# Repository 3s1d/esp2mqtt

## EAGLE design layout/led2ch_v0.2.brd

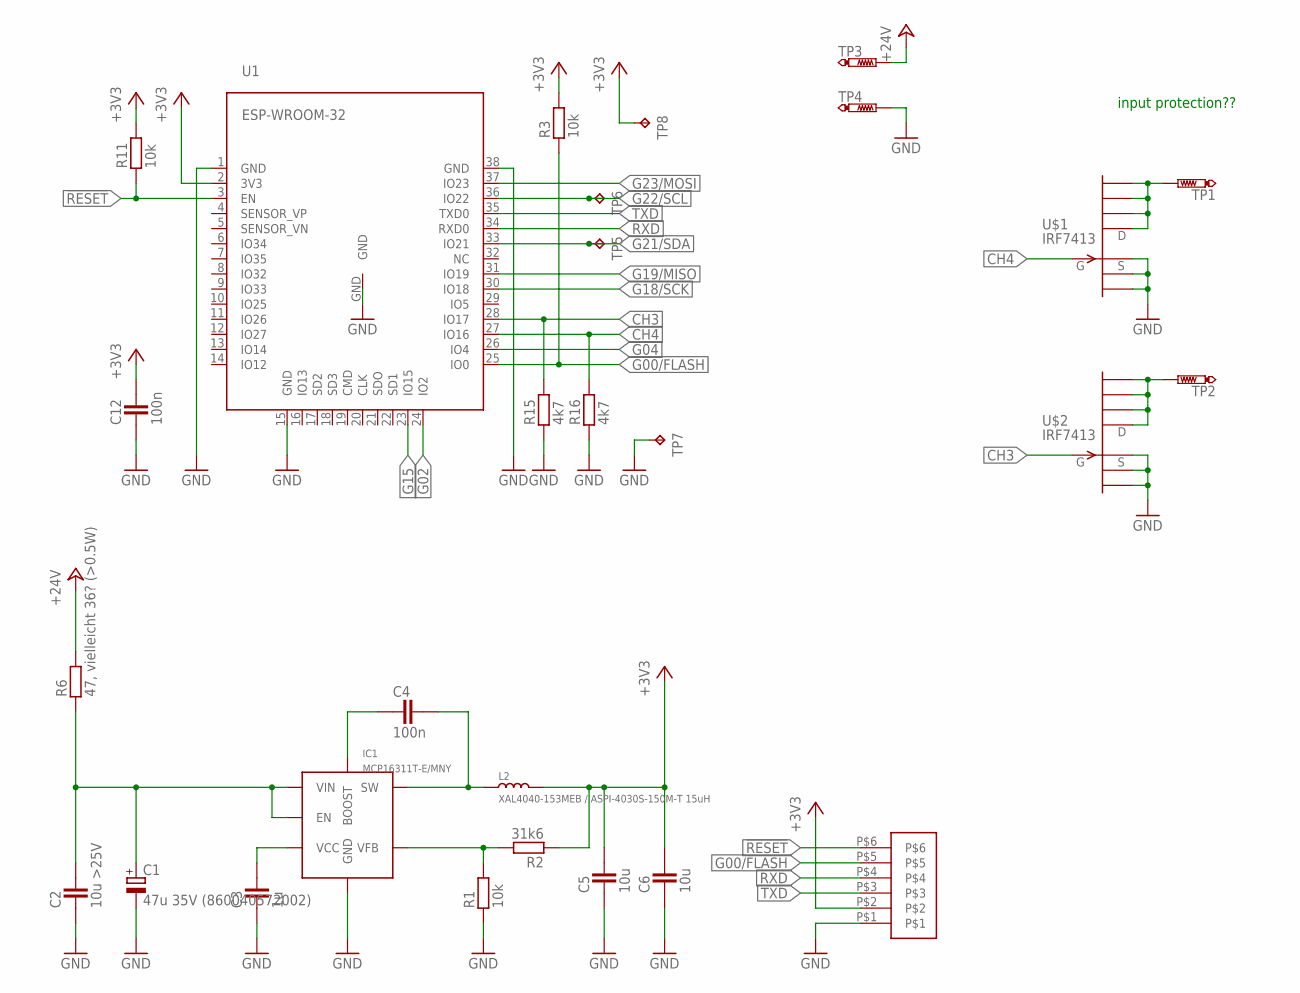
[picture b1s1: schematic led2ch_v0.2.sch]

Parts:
C1: 47u 35V (860040572002); E2-5
C2: 10u >25V; CAPC2012X145AN
C3: 1u; CAPC1608X92N
C4, C12: 100n; CAPC1005X60N
C5, C6: 10u; CAPC2012X145AN
IC1: MCP16311T-E/MNY; TDFN8
L2: XAL4040-153MEB / ASPI-4030S-150M-T 15uH; L0420
R1, R3, R11: 10k; RESC1005X40AN
R2: 31k6; RESC1005X40AN
R6: 47, vielleicht 36? (>0.5W); RESC3115X70N
R15, R16: 4k7; RESC1005X40AN
TP1, TP2: PTR1B1,27; B1,27
TP3, TP4: PTR1B2,54; B2,54
TP5, TP6, TP7, TP8: TPB1,27; B1,27
U1: ESP-WROOM-32
U$1, U$2: IRF7413; SO-8
U$3: 3X2-2.00RM

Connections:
!RESET: R11.1, U1.3 (EN), U$3.P$6
+3V3: C5.2, C6.2, C12.2, L2.2, R2.1, R3.2, R11.2, TP8.TP, U1.2 (3V3), U$3.P$2
+24V: R6.2, TP3.TP
CH3: R15.2, U1.28 (IO17), U$2.4 (G)
CH4: R16.2, U1.27 (IO16), U$1.4 (G)
G00/FLASH: R3.1, U1.25 (IO0), U$3.P$5
G02: U1.24 (IO2)
G04: U1.26 (IO4)
G15: U1.23 (IO15)
G18/SCK: U1.30 (IO18)
G19/MISO: U1.31 (IO19)
G21/SDA: TP5.TP, U1.33 (IO21)
G22/SCL: TP6.TP, U1.36 (IO22)
G23/MOSI: U1.37 (IO23)
GND: C1.-, C2.1, C3.1, C5.1, C6.1, C12.1, IC1.P$5 (GND), IC1.P$8 (GND), IC1.P$9 (GND), R1.1, R15.1, R16.1, TP4.TP, TP7.TP, U1.1 (GND), U1.15 (GND), U1.38 (GND), U1.GND, U$1.1 (S), U$1.2 (S1), U$1.3 (S2), U$2.1 (S), U$2.2 (S1), U$2.3 (S2), U$3.P$1
unnamed: C3.2, IC1.P$2 (VCC)
unnamed: C1.+, C2.2, IC1.P$3 (EN), IC1.P$4 (VIN), R6.1
unnamed: C4.1, IC1.P$7 (BOOST)
unnamed: C4.2, IC1.P$6 (SW), L2.1
unnamed: IC1.P$1 (VFB), R1.2, R2.2
unnamed: TP1.TP, U$1.5 (D), U$1.6 (D1), U$1.7 (D2), U$1.8 (D3)
unnamed: TP2.TP, U$2.5 (D), U$2.6 (D1), U$2.7 (D2), U$2.8 (D3)
RXD: U1.34 (RXD0), U$3.P$4
TXD: U1.35 (TXD0), U$3.P$3

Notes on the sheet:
input protection??

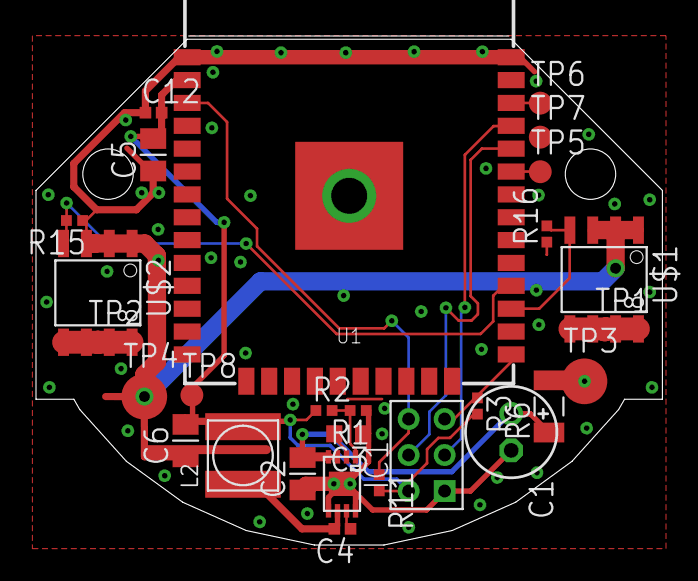
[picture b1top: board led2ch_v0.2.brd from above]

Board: 2 copper layers, 34.8 x 28.3 mm, 28 parts (0 on the bottom side), 18 nets.

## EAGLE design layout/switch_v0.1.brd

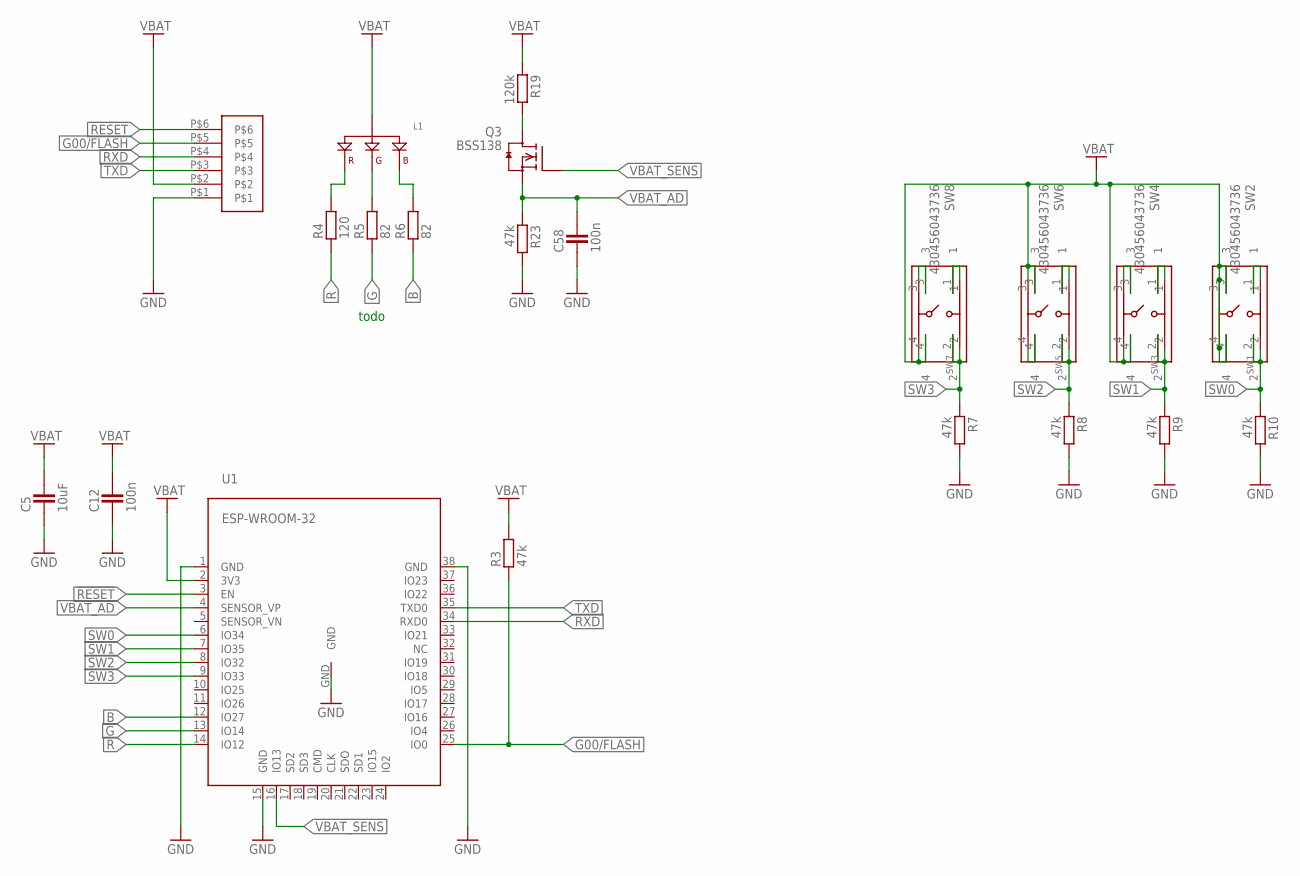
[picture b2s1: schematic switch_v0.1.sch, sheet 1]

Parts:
C5: 10uF; CAPC2012X145AN
C12, C58: 100n; CAPC1005X60N
L1: RGBLED_COMMONA; LEDRGB
Q3: BSS138; SOT23
R3, R7, R8, R9, R10, R23: 47k; RESC1005X40AN
R4: 120; RESC2012X70N
R5, R6: 82; RESC2012X70N
R19: 120k; RESC1005X40AN
SW1, SW3, SW5, SW7: 4301X20858X6
SW2, SW4, SW6, SW8: 430456043736
U1: ESP-WROOM-32
U$3: 3X2-2.00RM

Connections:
!RESET: U1.3 (EN), U$3.P$6; also elsewhere on the board
B: R6.1, U1.12 (IO27)
G: R5.1, U1.13 (IO14)
G00/FLASH: R3.1, U1.25 (IO0), U$3.P$5
GND: C5.1, C12.1, C58.1, R7.2, R8.2, R9.2, R10.2, R23.2, U1.1 (GND), U1.15 (GND), U1.38 (GND), U1.GND, U$3.P$1; also elsewhere on the board
unnamed: L1.1 (R), R4.2
unnamed: L1.3 (G), R5.2
unnamed: L1.4 (B), R6.2
unnamed: SW5.1, SW6.1
unnamed: SW5.4, SW6.4
unnamed: SW7.3, SW8.3
unnamed: SW7.1, SW8.1
unnamed: SW3.1, SW4.1
unnamed: SW3.3, SW4.3
unnamed: SW1.1, SW2.1
unnamed: Q3.3 (D), R19.2
R: R4.1, U1.14 (IO12)
RXD: U1.34 (RXD0), U$3.P$4
SW0: R10.1, SW1.2, SW2.2, U1.6 (IO34)
SW1: R9.1, SW3.2, SW4.2, U1.7 (IO35)
SW2: R8.1, SW5.2, SW6.2, U1.8 (IO32)
SW3: R7.1, SW7.2, SW8.2, U1.9 (IO33)
TXD: U1.35 (TXD0), U$3.P$3
VBAT: C5.2, C12.2, L1.2 (A), R3.2, R19.1, SW1.3, SW1.4, SW2.3, SW2.4, SW3.4, SW4.4, SW5.3, SW6.3, SW7.4, SW8.4, U1.2 (3V3), U$3.P$2; also elsewhere on the board
VBAT_AD: C58.2, Q3.2 (S), R23.1, U1.4 (SENSOR_VP)
VBAT_SENS: Q3.1 (G), U1.16 (IO13)

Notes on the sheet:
todo

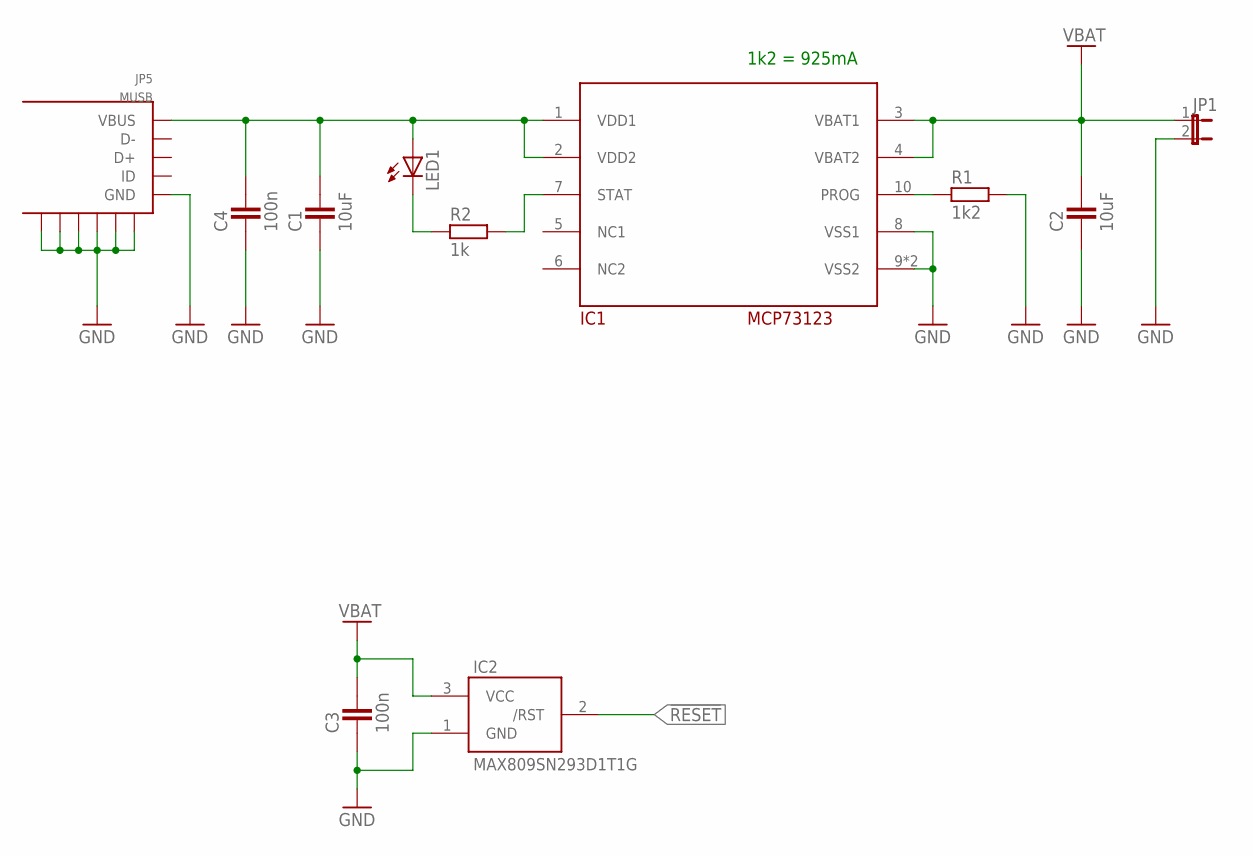
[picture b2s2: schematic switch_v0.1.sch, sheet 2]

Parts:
C1, C2: 10uF; CAPC2012X145AN
C3, C4: 100n; CAPC1005X60N
IC1: MCP73123; DFN10-3X3
IC2: MAX809SN293D1T1G; SOT23
JP1: JP1E; JP1
JP5: MUSB; MICRO-USB
LED1: LEDCHIPLED_0805; CHIPLED_0805
R1: 1k2; RESC1005X40AN
R2: 1k; RESC1005X40AN

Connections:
!RESET: IC2.2 (/RST); also elsewhere on the board
GND: C1.1, C2.1, C3.1, C4.1, IC1.8 (VSS1), IC1.9 (VSS2), IC1.EXP (VSS2), IC2.1 (GND), JP1.2, JP5.G$1 (S1), JP5.G$2 (S2), JP5.G$3 (S3), JP5.G$4 (S4), JP5.P$5 (GND), JP5.S$1 (S5), JP5.S$2 (S6), R1.2; also elsewhere on the board
unnamed: C1.2, C4.2, IC1.1 (VDD1), IC1.2 (VDD2), JP5.P$1 (VBUS), LED1.A
unnamed: LED1.C, R2.1
unnamed: IC1.7 (STAT), R2.2
unnamed: IC1.10 (PROG), R1.1
VBAT: C2.2, C3.2, IC1.3 (VBAT1), IC1.4 (VBAT2), IC2.3 (VCC), JP1.1; also elsewhere on the board

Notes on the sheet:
1k2 = 925mA

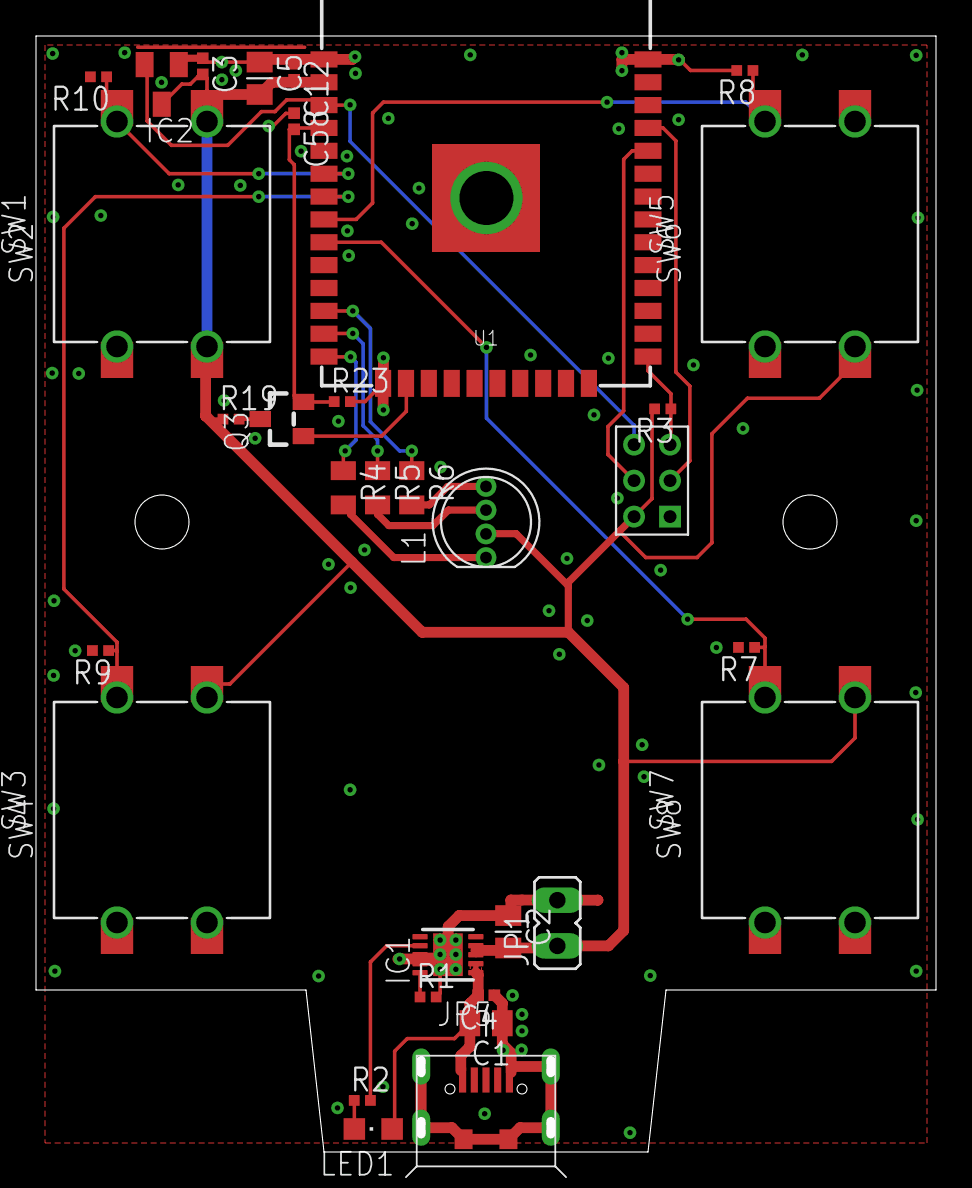
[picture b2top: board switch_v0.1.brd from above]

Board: 2 copper layers, 49.5 x 61.5 mm, 36 parts (0 on the bottom side), 30 nets.

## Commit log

2018-10-06 begin was removed somehow...
2018-11-11 minor changes
2018-11-11 added switch

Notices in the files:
parts and their libraries:
m-pad-2.1-mod: License : GNU General Public License version 2 (see bottom)
EAGLE-TACT_SWITCHES-rev1: Copyright: Würth Elektronik
supply0: Copyright (C) 2007, Bob Starr
